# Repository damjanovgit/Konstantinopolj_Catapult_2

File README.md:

# Konstantinopolj_Catapult_2
Микроконтролерски системи/Рачунарска електроника, зимски семестар, ак. 2022/2023. година
<br />
<br />
<p align="center">

# Упутство за повезивање катапулта

## Напајање плочице
<p align="justify">Како је задано и пројектним задатком, напајање које се доводи на плочицу износи 12 V. Напајање се у овом случају доводи са протоборда (кориштењем мултиметра претходно је  увијек неопходно провјерити да ли напајање доиста одговара 12 V), а на слици су приказана и минимална повезивања. Краткоспојник жуте боје одговара 12 V, док је плавим означено уземљење, као што се да примијетити на слици. 
<br />
<br />
<p align="center">

## Повезивање плочице са програматором 
<p align="justify">За програмирање микроконтролера користи се програматор PICkit верзије 3. Наредна слика показује pinout који користи овај програматор, при чему стрелица ка доле означава пин MCLR, односно, како је приказано ознакама на слици слијева:
<br />
<br />
<p align="center">

<p align="justify">На слици здесна приказано је повезивање програматора са плочицом. Пет конектора на које треба повезати пинове програматора налази се унутар црвеног блока, те редослијед који је претходно поменут важи уколико вршимо повезивање као на слици.

## Повезивање корачних мотора са плочицом

<p align="justify">За рад са катапултом кориштено је шест корачних мотора. Од тог броја два корачна мотора користе се за кретање ласера, преостала четири су на самом катапулту,означени са О (окретање), N (натезање), К (кашика) те P (пуцање). Мотор са ознаком О омогућава окретање самог катапулта, а претходно поменути мотори са ознакама N, K и  P приказани су  на слици испод. 
<br />
<br />

Слиједи и повезивање корачних мотора са плочицом. На слици је приказан распоред повезивања, гдје се неозначени корачни мотори односе на ласере. 
<br />
<br />
<p align="center">

## Повезивање са рачунаром

<p align="justify">За везу са рачунаром  користи се USB-UART модул. Са претходно инсталираном верзијом одговарајућег драјвера за FT232RL неопходно је повезати рачунар и модул који се налази на плочици. 

<br />
<br />
<p align="center">

## Програмирање и управљање катапултом
<p align="justify">Преостаје  упалити напајање, а затим на плочици омогућити програмирање микроконтролера. Наредна слика приказује које краткоспојнике треба повезати приликом програмирања (смеђи и зелени), а затим и након што се микроконтролер успјешно испрограмира (црни и зелени). 
<br />
<br />
<p align="center">

<p align="justify">Пројекат у MikroC-у (фолдер Software/PIC24) компајлирати, а затим изгенерисан .hex унијети у MPLAB IDE софтвер за програмирање. Ући у апликацију (софтвер Processing) и учитати пројекат (фолдер Software/Processing), да би  се затим управљало катапултом, са контролним командама наведеним у табели испод.
<br />
<br />

|  Команда |         Функционалност          
|----------|---------------------------------
|  А или а | помјерање првог ласера улијево  
|  D или d | помјерање првог ласера удесно
|  J или j | помјерање другог ласера улијево 
|  L или l | помјерање другог ласера удесно
|  C или c | калибрација
|  S или s | синхронизација ласера са апликациjом
|  space   | гађање мете

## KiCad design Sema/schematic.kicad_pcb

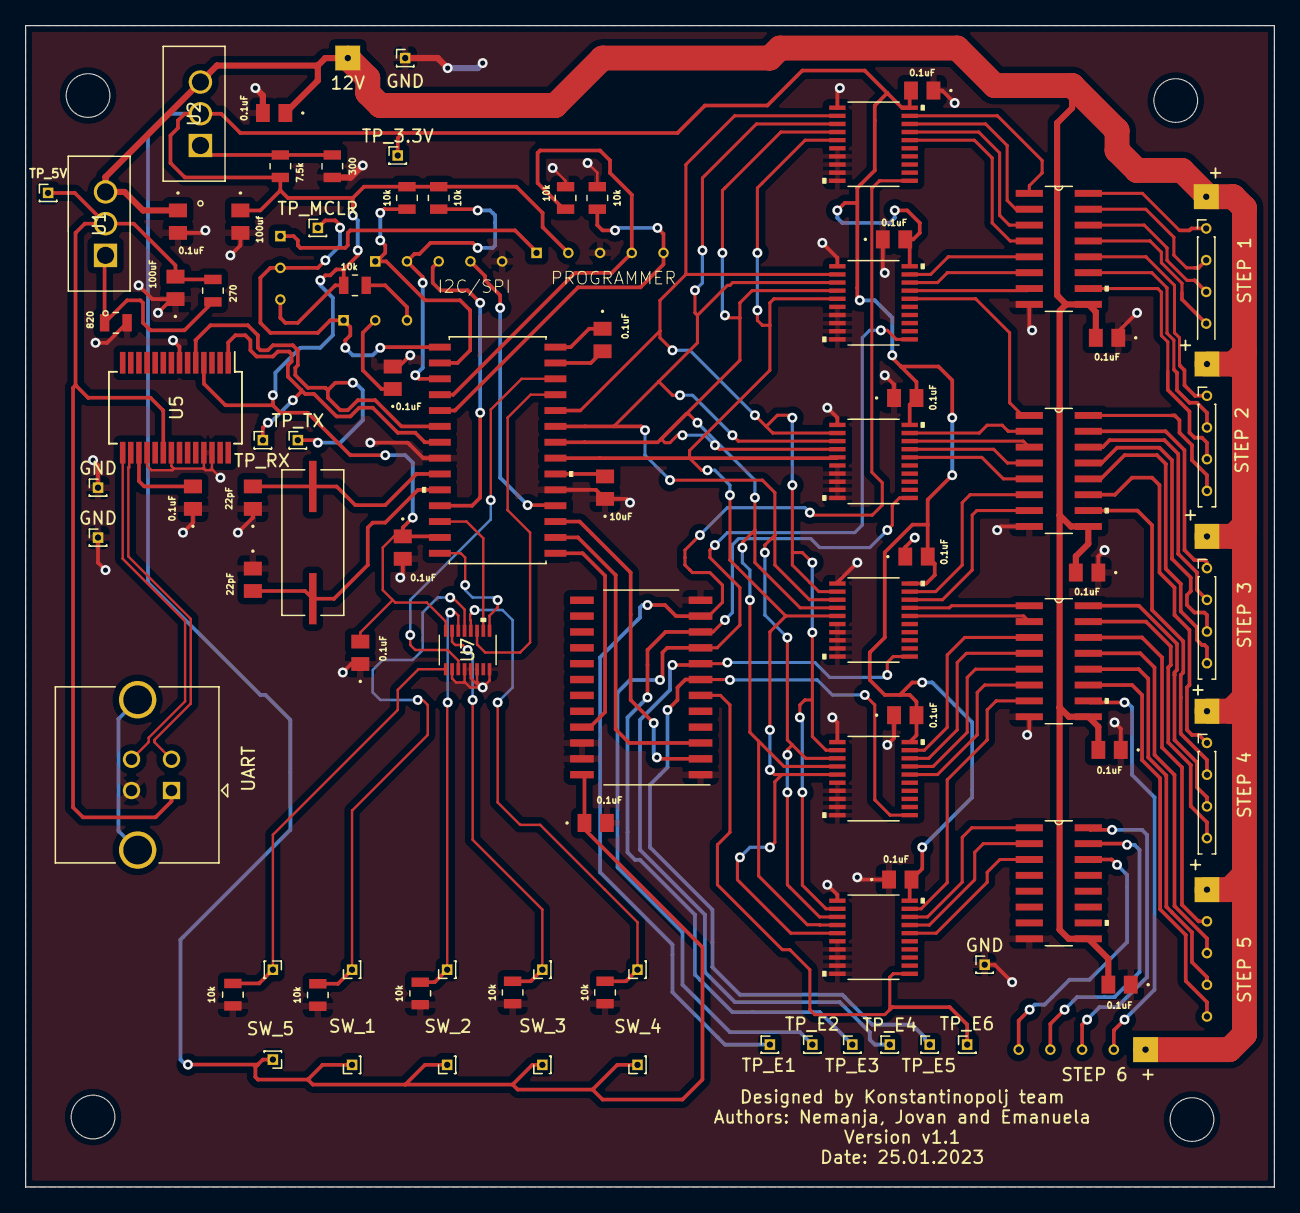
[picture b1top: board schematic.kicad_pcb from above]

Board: 2 copper layers, 100.0 x 93.0 mm, 95 parts (0 on the bottom side), 96 nets.

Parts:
0.1uF1: 0.1uF; 08055A220JAT2A
12V: Conn_01x01_Male; PinHeader_1x01_P1.00mm_Vertical
C1, C5, C6, C8, C9, C10, C11, C13, C14, C15, C16, C17, C18, C19, C20, C21, C22: 0.1uF; 08055A220JAT2A
C2: 100uF; 08055A220JAT2A
C3, C4: 22pF; 08055A220JAT2A
C7: 100uf; 08055A220JAT2A
C12: 10uF; 08055A220JAT2A
GND: Conn_01x01_Male; PinHeader_1x01_P1.00mm_Vertical
GND#2, GND#3, GND#4: Conn_01x01_Male; PinHeader_1x01_P1.00mm_Vertical
H1, H2, H3, H4: MountingHole; MountingHole_3.5mm
J1, J4, J7, J8, J9, J10, J11, J12: Conn_01x05_Male; PinHeader_1x05_P1.00mm_Vertical
J3, J5: Conn_01x03_Male; PinHeader_1x03_P1.00mm_Vertical
R1, R2, R7, R8, R9, R10, R11, R12, R13, R14: 10k; HCJ0805ZT0R00
R3: 270; HCJ0805ZT0R00
R4: 820; HCJ0805ZT0R00
R5: 300; HCJ0805ZT0R00
R6: 7.5k; HCJ0805ZT0R00
SW_1, SW_2, SW_3, SW_4, SW_5: TestPoint_Small; PinHeader_1x01_P1.00mm_Vertical
TP1.1, TP2.1, TP3.1, TP4.1, TP5.1: TestPoint_Small; PinHeader_1x01_P1.00mm_Vertical
TP_3.3V, TP_5V: TestPoint; PinHeader_1x01_P1.00mm_Vertical
TP_E1, TP_E2, TP_E3, TP_E4, TP_E5, TP_E6: TestPoint; PinHeader_1x01_P1.00mm_Vertical
TP_MCLR: TestPoint; PinHeader_1x01_P1.00mm_Vertical
TP_RX: TestPoint; PinHeader_1x01_P1.00mm_Vertical
TP_TX: TestPoint; PinHeader_1x01_P1.00mm_Vertical
U1, U2: LM317AT/NOPB; LM317AT
U3: PIC24FJ64GA702-I/SO; PIC24FJ64GA702-I&slash_SO
U4: ABLS-8.000MHZ-B2-T
U5: FT232RL; SSOP-28_5.3x10.2mm_P0.65mm
U6: CD74HC4514M96
U7: PTMUX1308QDYYRQ1
U8, U9, U10, U11, U12, U13: 74LVT573MTC
U14, U15, U16, U17: ULN2003AIDR
UART: USB_B; USB_B_TE_5787834_Vertical

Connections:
3.3V: 0.1uF1.2, C5.1, C7.1, C10.1, C13.2, C14.2, C15.2, C16.2, C17.2, C18.2, J3.3, J4.2, R1.1, R2.1, R6.2, R7.1, SW_1.1, SW_2.1, SW_3.1, SW_4.1, SW_5.1, TP_3.3V.1, U2.2 (OUT), U3.13 (VDD), U5.4 (VCCIO), U6.24 (VCC), U7.16 (VDD), U8.20 (VCC), U9.20 (VCC), U10.20 (VCC), U11.20 (VCC), U12.20 (VCC), U13.20 (VCC)
5V: C2.2, R3.2, TP_5V.1, U1.2 (OUT), U5.20 (VCC), UART.1 (VBUS)
12V: 12V.1, C1.1, C8.1, C19.2, C20.2, C21.2, C22.2, J7.1, J8.1, J9.1, J10.1, J11.1, J12.1, U1.3 (IN), U2.3 (IN), U14.9 (COM), U15.9 (COM), U16.9 (COM), U17.9 (COM)
A0: U3.17 (TCK/RP8/SCL1/OCM1B/CTED10/RB8), U6.2 (A0)
A1: U3.16 (RP7/OCM1A/CTED3/INT0/RB7), U6.3 (A1)
A2: U3.15 (PGC3/RP6/ASCL1/OCM1F/RB6), U6.21 (A2)
B1: J7.5, U14.13 (4C)
B2: J8.5, U15.16 (1C)
B3: J9.5, U15.12 (5C)
B4: J12.5, U16.15 (2C)
B5: J10.5, U16.11 (6C)
B6: J11.5, U17.14 (3C)
CS: J1.4, U3.18 (TDO/C1INC/C2INC/C3INC/TMPRN/RP9/SDA1/T1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)
D1: U3.24 (AN7/C1INC/RP13/OCM1D/CTPLS/RB13), U8.2 (D0), U9.2 (D0), U10.2 (D0), U11.2 (D0), U12.2 (D0), U13.2 (D0)
D2: U3.23 (AN8/LVDIN/RP12/RB12), U8.3 (D1), U9.3 (D1), U10.3 (D1), U11.3 (D1), U12.3 (D1), U13.3 (D1)
D3: U3.22 (PGC2/TMS/REFI1/RP11/CTED9/RB11), U8.4 (D2), U9.4 (D2), U10.4 (D2), U11.4 (D2), U12.4 (D2), U13.4 (D2)
D4: U3.21 (PGD2/TDI/RP10/OCM1C/CTED11/RB10), U8.5 (D3), U9.5 (D3), U10.5 (D3), U11.5 (D3), U12.5 (D3), U13.5 (D3)
D+: U5.15 (USBD+), UART.3 (D+)
D-: U5.16 (USBD-), UART.2 (D-)
E1: TP_E1.1, U6.11 (Y0), U8.11 (LE)
E2: TP_E2.1, U6.9 (Y1), U9.11 (LE)
E3: TP_E3.1, U6.10 (Y2), U10.11 (LE)
E4: TP_E4.1, U6.8 (Y3), U11.11 (LE)
E5: TP_E5.1, U6.7 (Y4), U12.11 (LE)
E6: TP_E6.1, U6.6 (Y5), U13.11 (LE)
GND: 0.1uF1.1, C1.2, C2.1, C3.1, C4.1, C5.2, C6.2, C7.2, C8.2, C9.1, C10.2, C12.1, C13.1, C14.1, C15.1, C16.1, C17.1, C18.1, C19.1, C20.1, C21.1, C22.1, GND.1, GND#2.1, GND#3.1, GND#4.1, J1.5, J4.3, R4.1, R5.1, R8.2, R9.2, R10.1, R11.1, R12.1, R13.1, R14.1, U3.8 (VSS), U3.19 (VSS), U5.7 (GND), U5.18 (GND), U5.21 (GND), U5.25 (AGND), U5.26 (TEST), U6.1 (LE_N), U6.12 (GND), U6.22 (A3), U6.23 (E_N), U7.2 (S6), U7.4 (S7), U7.5 (S5), U7.6 (EN), U7.8 (GND), U8.1 (OE_N), U8.6 (D4), U8.7 (D5), U8.8 (D6), U8.9 (D7), U8.10 (GND), U9.1 (OE_N), U9.6 (D4), U9.7 (D5), U9.8 (D6), U9.9 (D7), U9.10 (GND), U10.1 (OE_N), U10.6 (D4), U10.7 (D5), U10.8 (D6), U10.9 (D7), U10.10 (GND), U11.1 (OE_N), U11.6 (D4), U11.7 (D5), U11.8 (D6), U11.9 (D7), U11.10 (GND), U12.1 (OE_N), U12.6 (D4), U12.7 (D5), U12.8 (D6), U12.9 (D7), U12.10 (GND), U13.1 (OE_N), U13.6 (D4), U13.7 (D5), U13.8 (D6), U13.9 (D7), U13.10 (GND), U14.8 (E), U15.8 (E), U16.8 (E), U17.8 (E), UART.4 (GND)
M: U3.26 (AN9/C3INA/RP15/CTED6/RB15), U7.3 (D)
MISO: J1.3, U3.11 (SOSCI/RP4/RB4)
MOSI: J1.2, R2.2, U3.3 (VREF-/CVREF-/AN1/C3IND/RP27/CTED2/RA1)
unnamed: C6.1, J5.2
unnamed: C9.2, U5.17 (3V3OUT)
unnamed: C11.1, U3.28 (AVDD/VDD)
unnamed: C11.2, U3.27 (AVSS/VSS)
unnamed: C12.2, U3.20 (VCAP)
unnamed: J3.1, J4.1
unnamed: J3.2, J5.1, TP_MCLR.1, U3.1 (*MCLR)
unnamed: J5.3, R7.2
unnamed: R3.1, R4.2, U1.1 (ADJ)
unnamed: R5.2, R6.1, U2.1 (ADJ)
O1: J7.2, U14.16 (1C)
O2: J8.2, U14.12 (5C)
O3: J9.2, U15.15 (2C)
O4: J12.2, U15.11 (6C)
O5: J10.2, U16.14 (3C)
O6: J11.2, U16.10 (7C)
OSCI: C3.2, U3.9 (OSCI/CLKI/C1IND/RA2), U4.1
OSCO: C4.2, U3.10 (OSCO/CLKO/C2IND/RA3), U4.2
P1: R10.2, TP1.1.1, U7.13 (S0)
P2: R11.2, TP2.1.1, U7.14 (S1)
P3: R12.2, TP3.1.1, U7.15 (S2)
P4: R13.2, TP4.1.1, U7.12 (S3)
P5: R14.2, TP5.1.1, U7.1 (S4)
PGC: J4.5, R8.1, U3.5 (PGC1/AN1-/AN3/C2INA/RP1/CTED12/RB1)
PGD: J4.4, R9.1, U3.4 (PGD1/AN2/CTCMP/C2INB/RP0/RB0)
PI1: J7.4, U14.14 (3C)
PI2: J8.4, U14.10 (7C)
PI3: J9.4, U15.13 (4C)
PI4: J12.4, U16.16 (1C)
PI5: J10.4, U16.12 (5C)
PI6: J11.4, U17.15 (2C)
Q1.1: U8.19 (O0), U14.1 (1B)
Q1.2: U9.19 (O0), U14.5 (5B)
Q1.3: U10.19 (O0), U15.2 (2B)
Q1.4: U11.19 (O0), U15.6 (6B)
Q1.5: U12.19 (O0), U16.3 (3B)
Q1.6: U13.19 (O0), U16.7 (7B)
Q2.1: U8.18 (01), U14.2 (2B)
Q2.2: U9.18 (01), U14.6 (6B)
Q2.3: U10.18 (01), U15.3 (3B)
Q2.4: U11.18 (01), U15.7 (7B)
Q2.5: U12.18 (01), U16.4 (4B)
Q2.6: U13.18 (01), U17.1 (1B)
Q3.1: U8.17 (02), U14.3 (3B)
Q3.2: U9.17 (02), U14.7 (7B)
Q3.3: U10.17 (02), U15.4 (4B)
Q3.4: U11.17 (02), U16.1 (1B)
Q3.5: U12.17 (02), U16.5 (5B)
Q3.6: U13.17 (02), U17.2 (2B)
Q4.1: U8.16 (03), U14.4 (4B)
Q4.2: U9.16 (03), U15.1 (1B)
Q4.3: U10.16 (03), U15.5 (5B)
Q4.4: U11.16 (03), U16.2 (2B)
Q4.5: U12.16 (03), U16.6 (6B)
Q4.6: U13.16 (03), U17.3 (3B)
RX: TP_RX.1, U3.7 (AN5/C1INA/RP3/SCL2/CTED8/RB3), U5.1 (TXD)
S0: U3.25 (CVREF/AN6/C3INB/RP14/CTED5/RB14), U7.11 (A0)
S1: U3.12 (SOSCO/PWRLCLK/RA4), U7.10 (A1)
S2: U3.14 (PGD3/RP5/ASDA1/OCM1E/RB5), U7.9 (A2)
SCL: J1.1, R1.2, U3.2 (VREF+/CVREF+/AN0/C3INC/RP26/CTED1/RA0)
Y1: J7.3, U14.15 (2C)
Y2: J8.3, U14.11 (6C)
Y3: J9.3, U15.14 (3C)
Y4: J12.3, U15.10 (7C)
Y5: J10.3, U16.13 (4C)
Y6: J11.3, U17.16 (1C)
tx: TP_TX.1, U3.6 (AN4/C1INB/RP2/SDA2/CTED13/RB2), U5.5 (RXD)

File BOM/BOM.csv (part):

Date:,31-1-2023,,,,,,,,,,,,,,,,,,
Tool:,Eeschema (6.0.2),,,,,,,,,,,,,,,,,,
Component Count:,95,,,,,,,,,,,,,,,,,,
,,,,,,,,,,,,,,,,,,,
Individual Components:,,,,,,,,,,,,,,,,,,,
,,,,,,,,,,,,,,,,,,,
Item,Qty,Reference(s),Value,Footprint,,,,,,,,,,,,,,,
,,C0,0.1uF,footprints:08055A220JAT2A,,,,,,,,,,,,,,,
,,C1,0.1uF,footprints:08055A220JAT2A,,,,,,,,,,,,,,,
,,C2,100uF,footprints:08055A220JAT2A,,,,,,,,,,,,,,,
,,C3,22pF,footprints:08055A220JAT2A,,,,,,,,,,,,,,,
,,C4,22pF,footprints:08055A220JAT2A,,,,,,,,,,,,,,,
,,C5,0.1uF,footprints:08055A220JAT2A,,,,,,,,,,,,,,,
,,C6,0.1uF,footprints:08055A220JAT2A,,,,,,,,,,,,,,,
,,C7,100uf,footprints:08055A220JAT2A,,,,,,,,,,,,,,,
,,C8,0.1uF,footprints:08055A220JAT2A,,,,,,,,,,,,,,,
,,C9,0.1uF,footprints:08055A220JAT2A,,,,,,,,,,,,,,,
,,C10,0.1uF,footprints:08055A220JAT2A,,,,,,,,,,,,,,,
,,C11,0.1uF,footprints:08055A220JAT2A,,,,,,,,,,,,,,,
,,C12,10uF,footprints:08055A220JAT2A,,,,,,,,,,,,,,,
,,C13,0.1uF,footprints:08055A220JAT2A,,,,,,,,,,,,,,,
,,C14,0.1uF,footprints:08055A220JAT2A,,,,,,,,,,,,,,,
,,C15,0.1uF,footprints:08055A220JAT2A,,,,,,,,,,,,,,,
,,C16,0.1uF,footprints:08055A220JAT2A,,,,,,,,,,,,,,,
,,C17,0.1uF,footprints:08055A220JAT2A,,,,,,,,,,,,,,,
,,C18,0.1uF,footprints:08055A220JAT2A,,,,,,,,,,,,,,,
,,C19,0.1uF,footprints:08055A220JAT2A,,,,,,,,,,,,,,,
,,C20,0.1uF,footprints:08055A220JAT2A,,,,,,,,,,,,,,,
,,C21,0.1uF,footprints:08055A220JAT2A,,,,,,,,,,,,,,,
,,C22,0.1uF,footprints:08055A220JAT2A,,,,,,,,,,,,,,,
,,H1,MountingHole,MountingHole:MountingHole_3.5mm,~,,,,,,,,,,,,,,
,,H2,MountingHole,MountingHole:MountingHole_3.5mm,~,,,,,,,,,,,,,,
,,H3,MountingHole,MountingHole:MountingHole_3.5mm,~,,,,,,,,,,,,,,
,,H4,MountingHole,MountingHole:MountingHole_3.5mm,~,,,,,,,,,,,,,,
,,J1,Conn_01x05_Male,Connector_PinHeader_1.00mm:PinHeader_1x05_P1.00mm_Vertical,~,,,,,,,,,,,,,,
,,J2,Conn_01x01_Male,Connector_PinHeader_1.00mm:PinHeader_1x01_P1.00mm_Vertical,~,,,,,,,,,,,,,,
,,J3,Conn_01x03_Male,Connector_PinHeader_1.00mm:PinHeader_1x03_P1.00mm_Vertical,~,,,,,,,,,,,,,,
,,J4,Conn_01x05_Male,Connector_PinHeader_1.00mm:PinHeader_1x05_P1.00mm_Vertical,~,,,,,,,,,,,,,,
,,J5,Conn_01x03_Male,Connector_PinHeader_1.00mm:PinHeader_1x03_P1.00mm_Vertical,~,,,,,,,,,,,,,,
,,J6,USB_B,Connector_USB:USB_B_TE_5787834_Vertical, ~,,,,,,,,,,,,,,
,,J7,Conn_01x05_Male,Connector_PinHeader_1.00mm:PinHeader_1x05_P1.00mm_Vertical,~,,,,,,,,,,,,,,
,,J8,Conn_01x05_Male,Connector_PinHeader_1.00mm:PinHeader_1x05_P1.00mm_Vertical,~,,,,,,,,,,,,,,
,,J9,Conn_01x05_Male,Connector_PinHeader_1.00mm:PinHeader_1x05_P1.00mm_Vertical,~,,,,,,,,,,,,,,
,,J10,Conn_01x05_Male,Connector_PinHeader_1.00mm:PinHeader_1x05_P1.00mm_Vertical,~,,,,,,,,,,,,,,
,,J11,Conn_01x05_Male,Connector_PinHeader_1.00mm:PinHeader_1x05_P1.00mm_Vertical,~,,,,,,,,,,,,,,
,,J12,Conn_01x05_Male,Connector_PinHeader_1.00mm:PinHeader_1x05_P1.00mm_Vertical,~,,,,,,,,,,,,,,
,,J13,Conn_01x01_Male,Connector_PinHeader_1.00mm:PinHeader_1x01_P1.00mm_Vertical,~,,,,,,,,,,,,,,
,,J14,Conn_01x01_Male,Connector_PinHeader_1.00mm:PinHeader_1x01_P1.00mm_Vertical,~,,,,,,,,,,,,,,
,,J15,Conn_01x01_Male,Connector_PinHeader_1.00mm:PinHeader_1x01_P1.00mm_Vertical,~,,,,,,,,,,,,,,
,,J16,Conn_01x01_Male,Connector_PinHeader_1.00mm:PinHeader_1x01_P1.00mm_Vertical,~,,,,,,,,,,,,,,
,,R1,10k,HCJ0805ZT0R00j:HCJ0805ZT0R00,,,,,,,,,,,,,,,
,,R2,10k,HCJ0805ZT0R00j:HCJ0805ZT0R00,,,,,,,,,,,,,,,
,,R3,270,HCJ0805ZT0R00j:HCJ0805ZT0R00,,,,,,,,,,,,,,,
,,R4,820,HCJ0805ZT0R00j:HCJ0805ZT0R00,,,,,,,,,,,,,,,
,,R5,300,HCJ0805ZT0R00j:HCJ0805ZT0R00,,,,,,,,,,,,,,,
,,R6,7.5k,HCJ0805ZT0R00j:HCJ0805ZT0R00,,,,,,,,,,,,,,,
,,R7,10k,HCJ0805ZT0R00j:HCJ0805ZT0R00,,,,,,,,,,,,,,,
,,R8,10k,HCJ0805ZT0R00j:HCJ0805ZT0R00,,,,,,,,,,,,,,,
,,R9,10k,HCJ0805ZT0R00j:HCJ0805ZT0R00,,,,,,,,,,,,,,,
,,R10,10k,HCJ0805ZT0R00j:HCJ0805ZT0R00,,,,,,,,,,,,,,,
,,R11,10k,HCJ0805ZT0R00j:HCJ0805ZT0R00,,,,,,,,,,,,,,,
,,R12,10k,HCJ0805ZT0R00j:HCJ0805ZT0R00,,,,,,,,,,,,,,,
,,R13,10k,HCJ0805ZT0R00j:HCJ0805ZT0R00,,,,,,,,,,,,,,,
,,R14,10k,HCJ0805ZT0R00j:HCJ0805ZT0R00,,,,,,,,,,,,,,,
,,TP1,TestPoint,Connector_PinHeader_1.00mm:PinHeader_1x01_P1.00mm_Vertical,~,,,,,,,,,,,,,,
,,TP1.1,TestPoint_Small,Connector_PinHeader_1.00mm:PinHeader_1x01_P1.00mm_Vertical,~,,,,,,,,,,,,,,
,,TP1.2,TestPoint_Small,Connector_PinHeader_1.00mm:PinHeader_1x01_P1.00mm_Vertical,~,,,,,,,,,,,,,,
,,TP2,TestPoint,Connector_PinHeader_1.00mm:PinHeader_1x01_P1.00mm_Vertical,~,,,,,,,,,,,,,,
,,TP2.1,TestPoint_Small,Connector_PinHeader_1.00mm:PinHeader_1x01_P1.00mm_Vertical,~,,,,,,,,,,,,,,
,,TP2.2,TestPoint_Small,Connector_PinHeader_1.00mm:PinHeader_1x01_P1.00mm_Vertical,~,,,,,,,,,,,,,,
,,TP3,TestPoint,Connector_PinHeader_1.00mm:PinHeader_1x01_P1.00mm_Vertical,~,,,,,,,,,,,,,,
,,TP3.1,TestPoint_Small,Connector_PinHeader_1.00mm:PinHeader_1x01_P1.00mm_Vertical,~,,,,,,,,,,,,,,
,,TP3.2,TestPoint_Small,Connector_PinHeader_1.00mm:PinHeader_1x01_P1.00mm_Vertical,~,,,,,,,,,,,,,,
,,TP4,TestPoint,Connector_PinHeader_1.00mm:PinHeader_1x01_P1.00mm_Vertical,~,,,,,,,,,,,,,,
,,TP4.1,TestPoint_Small,Connector_PinHeader_1.00mm:PinHeader_1x01_P1.00mm_Vertical,~,,,,,,,,,,,,,,
,,TP4.2,TestPoint_Small,Connector_PinHeader_1.00mm:PinHeader_1x01_P1.00mm_Vertical,~,,,,,,,,,,,,,,
,,TP5,TestPoint,Connector_PinHeader_1.00mm:PinHeader_1x01_P1.00mm_Vertical,~,,,,,,,,,,,,,,
,,TP5.1,TestPoint_Small,Connector_PinHeader_1.00mm:PinHeader_1x01_P1.00mm_Vertical,~,,,,,,,,,,,,,,
,,TP5.2,TestPoint_Small,Connector_PinHeader_1.00mm:PinHeader_1x01_P1.00mm_Vertical,~,,,,,,,,,,,,,,
,,TP6,TestPoint,Connector_PinHeader_1.00mm:PinHeader_1x01_P1.00mm_Vertical,~,,,,,,,,,,,,,,
,,TP7,TestPoint,Connector_PinHeader_1.00mm:PinHeader_1x01_P1.00mm_Vertical,~,,,,,,,,,,,,,,
,,TP8,TestPoint,Connector_PinHeader_1.00mm:PinHeader_1x01_P1.00mm_Vertical,~,,,,,,,,,,,,,,
,,TP9,TestPoint,Connector_PinHeader_1.00mm:PinHeader_1x01_P1.00mm_Vertical,~,,,,,,,,,,,,,,
,,TP10,TestPoint,Connector_PinHeader_1.00mm:PinHeader_1x01_P1.00mm_Vertical,~,,,,,,,,,,,,,,
,,TP11,TestPoint,Connector_PinHeader_1.00mm:PinHeader_1x01_P1.00mm_Vertical,~,,,,,,,,,,,,,,
,,U1,LM317AT/NOPB,LM317AT:LM317AT,,,,,,,,,,,,,,,
,,U2,LM317AT/NOPB,LM317AT:LM317AT,,,,,,,,,,,,,,,
,,U3,PIC24FJ64GA702-I/SO,PIC24FJ64GA702-ISO:PIC24FJ64GA702-I&slash_SO,,,,,,,,,,,,,,,
,,U4,ABLS-8.000MHZ-B2-T,ABLS-8:ABLS-8.000MHZ-B2-T,,,,,,,,,,,,,,,
,,U5,FT232RL,Package_SO:SSOP-28_5.3x10.2mm_P0.65mm,,,,,,,,,,,,,,,
,,U6,CD74HC4514M96,CD74HC4514M96j:CD74HC4514M96,,,,,,,,,,,,,,,
,,U7,PTMUX1308QDYYRQ1,PTMUX1308QDYYRQ1j:PTMUX1308QDYYRQ1,,,,,,,,,,,,,,,
,,U8,74LVT573MTC,74LVT573MTCj:74LVT573MTC,,,,,,,,,,,,,,,
,,U9,74LVT573MTC,74LVT573MTCj:74LVT573MTC,,,,,,,,,,,,,,,
,,U10,74LVT573MTC,74LVT573MTCj:74LVT573MTC,,,,,,,,,,,,,,,
,,U11,74LVT573MTC,74LVT573MTCj:74LVT573MTC,,,,,,,,,,,,,,,
,,U12,74LVT573MTC,74LVT573MTCj:74LVT573MTC,,,,,,,,,,,,,,,
,,U13,74LVT573MTC,74LVT573MTCj:74LVT573MTC,,,,,,,,,,,,,,,
,,U14,ULN2003AIDR,ULN2003AIDRj:ULN2003AIDR,,,,,,,,,,,,,,,
,,U15,ULN2003AIDR,ULN2003AIDRj:ULN2003AIDR,,,,,,,,,,,,,,,
,,U16,ULN2003AIDR,ULN2003AIDRj:ULN2003AIDR,,,,,,,,,,,,,,,
,,U17,ULN2003AIDR,ULN2003AIDRj:ULN2003AIDR,,,,,,,,,,,,,,,
,,,,,,,,,,,,,,,,,,,
,,,,,,,,,,,,,,,,,,,
,,,,,,,,,,,,,,,,,,,
Collated Components:,,,,,,,,,,,,,,,,,,,
,,,,,,,,,,,,,,,,,,,
Item,Qty,Reference(s),Value,Footprint,Mouser Part No.,Link to Mouser,,,,,,,,,,,,,
1,1,C0,0.1uF,footprints:08055A220JAT2A,80-C0805C104K5RACLR,https://eu.mouser.com/ProductDetail/KEMET/C0805C104K5RAC7411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,,,,,,,,,,,,,
2,17,"C1, C5, C6, C8, C9, C10, C11, C13, C14, C15, C16, C17, C18, C19, C20, C21, C22",0.1uF,footprints:08055A220JAT2A,80-C0805C104K5RACLR,,,,,,,,,,,,,,
3,1,C2,100uF,footprints:08055A220JAT2A,581-08056D107MAT2A,https://eu.mouser.com/ProductDetail/KYOCERA-AVX/08056D107MAT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,,,,,,,,,,,,,
4,2,"C3, C4",22pF,footprints:08055A220JAT2A,581-08055A220J,https://eu.mouser.com/ProductDetail/KYOCERA-AVX/08055A220JAT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,,,,,,,,,,,,,
5,1,C7,100uf,footprints:08055A220JAT2A,581-08056D107MAT2A,,,,,,,,,,,,,,
6,1,C12,10uF,footprints:08055A220JAT2A,581-0805YC106KAT2A,https://eu.mouser.com/ProductDetail/KYOCERA-AVX/0805YC106KAT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,,,,,,,,,,,,,
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
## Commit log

2022-12-30 Uradjena sema
2023-01-07 Dodata Proteus simulacija u folderu Proteus simulacija
2023-01-07 Prepravljen Proteus projekat
2023-01-11 Rutiran PCB Prepravljena šema u skladu sa zahtjevima
2023-01-11 BOM fajl
2023-01-12 Dodana tehnicka dokumentacija komponenti
2023-01-18 Dodat peti prekidac i u folderu Datasheet komponenti dodat datasheet koristenog multipleksera
2023-01-18 Dodat bajpas kondezator na ulaze za napajanje multipleksera
2023-01-25 Finalna verzija layout-a
2023-01-25 Napisane labele na ploci
2023-01-25 Male izmjene oko labela
2023-01-25 Brisanje nezeljenog datasheet-a
2023-01-30 Izmjene na layout-u
2023-01-30 Dodavanje labela
2023-01-31 Final version
2023-01-31 Azuriran BOM fajl sa siframa i linkovima sa Mouser-a
2023-01-31 Dodana preostala dokumentacija
2023-02-08 Izmjene u BOM fajlu
2023-02-08 Prethodna verzija BOM je obrisana
2023-04-08 Dodate su pocetne verzije kodova (software-a) za upravljanjem katapultom
2023-04-10 v0.1: - Pocetni kod za naginjanje
2023-04-14 v0.2
2023-04-14 v0.3
2023-04-18 v0.4
2023-04-18 v0.5
2023-04-20 Editovan readme fajl
2023-04-20 Manje izmjene u readme fajlu
2023-04-22 v0.6
2023-04-22 Dodata nova komanda u tabeli
2023-04-23 Manje ispravke u tekstu
2023-04-24 v0.7
2023-04-26 v0.8
2023-04-27 Revert "Software"
2023-04-27 Ispravljena mala greska
2023-04-27 Dodana video prezentacija projektnog zadatka

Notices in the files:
parts and their libraries:
Copyright 2021 Accelerated Designs. All rights reserved.
